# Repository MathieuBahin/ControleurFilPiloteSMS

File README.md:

# Controleur radiateur avec fil pilote par SMS

Bonjour à tous je vous propose aujourd'hui un projet pour contrôler un radiateur par SMS. Le radiateur doit posséder l'option "Fil pilote".

Mon besoin est de pouvoir piloter la mise en marche d'un radiateur situé dans une résidence secondaire à distance. L'idée est de pouvoir envoyer un ordre à une unité réceptrice qui va allumer le radiateur et me permettre d'arriver 1/2 jours plus tard avec une température correcte dans la résidence.

Des produits similaires existent mais la plupart proposent une communication par Internet, non compatible avec la configuration de la résidence secondaire.

Attention vous allez manipuler des courants mortels je vous conseille une grande vigilance lors des manipulations.

## Electronique

### La communication par fil pilote
On retrouve ci-dessous les commandes pour piloter le radiateur :

[Source](https://www.planete-domotique.com/blog/2012/01/05/piloter-un-radiateur-grace-a-son-fil-pilote/)

Le radiateur est donc piloté grâce à la sinusoïde 230V.

Pour créer les demi-alternances positives et négatives on utilise les optocoupleurs et les diodes.

En effet une diode dans le sens passant du 230V créer une demi-alternance positive et une diode dans le sens non passant crée une demi-alternance négative. Les optocoupleurs permettent de choisir si le chemin positif, négatif ou les deux sont utilisés.

### Composants utilisés
Pour le projet voici les composants utilisés : 

| Nom                  |  Coût |
| --------------------- |:-----:|
| Arduino Nano x1          |   2€  |
| [SIM800L](https://www.amazon.fr/Sim800l-Quadribande-Embarqu%C3%A9e-Antenne-Arduino/dp/B01FQPLG9W) x1     | 6€ |
| [DS18B20](https://www.amazon.fr/ANGEEK-capteurs-temp%C3%A9rature-num%C3%A9riques-TO92-55%C2%B0C/dp/B07VB25GS5/) x1        |  8€ pour 5 |
| [IRM-10-5](https://fr.rs-online.com/web/p/alimentations-a-decoupage/1358929/)    x1        |  10€   |
| [ZFKDS gauche](https://fr.rs-online.com/web/p/borniers-pour-circuits-imprimes/8045105/)  x1    | 0.50€ |
| [ZFKDS droit](https://fr.rs-online.com/web/p/borniers-pour-circuits-imprimes/8045102/)   x1  | 16.70€ pour 50 |
| [MOC3043M](https://fr.rs-online.com/web/p/optocoupleurs/1611159) x2    | 7.76€ pour 10 |
| Résistance 4.7k     | |
| Résistance 1.8k     | |
| Résistance 1k     | |
| Résistance 680     | |
| Diode 1N4007 x3    | |
| Condensateur 470µF [Farnell](https://fr.farnell.com/panasonic-electronic-components/eeufr0j471/condensateur-470-f-6-3v-20/dp/2805615)     | |

Le capteur de température et la résistance R9 associée sont optionnels.
Les connecteurs ZFKDS peuvent être remplacés par des borniers etc.
Le condensateur n'est pas optionnel.
Le microcontrôleur Arduino est remplaçable par d'autres (par exemple un PIC8F ou autres) mais le code ne sera pas portable sur les autres plateformes telles quelles.

## Projet KiCad
Les fichiers KiCad sont situés dans le dossier KiCad. Les PCB sont gravés chez [JLCPCB](https://jlcpcb.com/).

Attention pour le module SIM800L a la tension d'alimentation qui est spéciale. J'utilise la tension de chute de la diode pour l'alimenter selon la datasheet. Un pont diviseur est également nécessaire pour la communication UART (5V → 3.3V).

Une fois le PCB reçu je vous conseille de souder le transformateur en dernier.

Si vous souhaitez faire une vérification sur le 230V à la sortie du fil pilote noté que votre multimètre ne vous indiquera pas 115V et si vous souhaitez vérifier avec un oscilloscope faite attention à utiliser une sonde différentielle !

## Développement Arduino
Vous pouvez utiliser l'IDE de votre choix j'utilise personnellement l'IDE Arduino.

Ajoutez les librairies dans votre dossier Arduino (généralement Documents\Arduino\libraries) sinon depuis l'IDE "Croquis → Inclure une bibliothèque"

Dans Outil choisissez votre carte : Arduino Nano et le processeur qui correspond à votre carte.

Puis connectez votre Arduino et flashez le programme.

Vous pouvez ouvrir le moniteur série à 9600 pour voir l'initialisation des composants.

Attention à remplir le numéro de téléphone ou vous souhaitez recevoir les sms. La carte SIM ne doit pas avoir de code PIN.

## Boitier

J'ai choisi un boitier de dérivation de 110x110mm. Vous pouvez soit fixer la carte électronique au fond avec des vis / écrous ou mettre un point de colle dans les coins.

## Installation

N'inversez pas la phase et le neutre, pour différencier les fils (en faisant très attention) munissez-vous de votre multimètre et prenez pour référence la terre.

Phase + terre environ égale à 230V

Neutre + terre environ égale à 0V

Le PCB n'a pas de protection contre les inversions, il est indispensable de brancher la phase sur l'entrée phase sinon le fil pilote ne fonctionnera pas. 

Sectionnez le fil de phase et le fil de neutre (en ayant disjoncté), ajouter un domino de 3 sur la phase et 3 sur le neutre. Branchez le fil pilote du radiateur directement sur la carte. La phase venant du mur va dans le domino qui repart en 2 fils, vers le boitier et vers le radiateur. Idem pour le neutre.

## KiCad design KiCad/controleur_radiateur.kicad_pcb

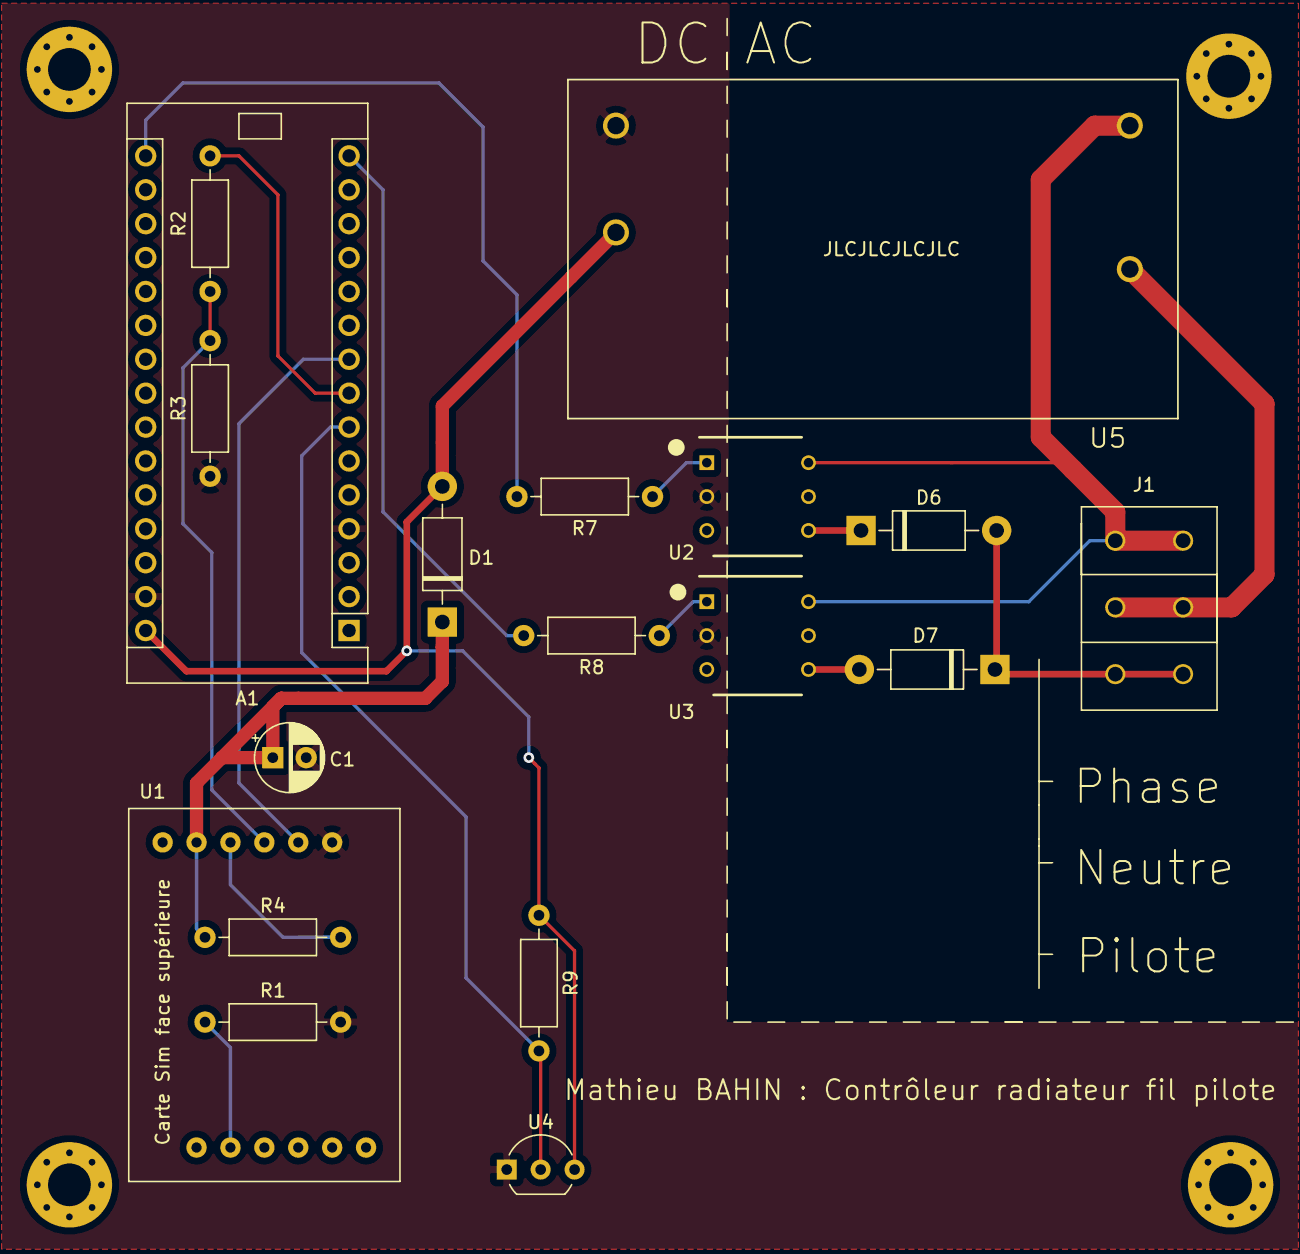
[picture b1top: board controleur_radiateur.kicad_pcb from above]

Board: 2 copper layers, 18 parts (0 on the bottom side), 18 nets.

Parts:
A1: Arduino_Nano_v3.x; Arduino_Nano_step
C1: 100u 10V; CP_Radial_D5.0mm_P2.50mm
D1, D6, D7: 1N4007; D_DO-41_SOD81_P10.16mm_Horizontal
J1: ZFKDS_3
R1, R4, R9: 4.7k; R_Axial_DIN0207_L6.3mm_D2.5mm_P10.16mm_Horizontal
R2: 1k; R_Axial_DIN0207_L6.3mm_D2.5mm_P10.16mm_Horizontal
R3: 1.8k; R_Axial_DIN0207_L6.3mm_D2.5mm_P10.16mm_Horizontal
R7, R8: 680; R_Axial_DIN0207_L6.3mm_D2.5mm_P10.16mm_Horizontal
U1: SIM800L; SIM800L_module
U2, U3: MOC3023M
U4: DS18B20; TO-92_Inline_Wide
U5: IRM-10-5

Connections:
+5V: A1.30, D1.2, R9.1, U4.3, U5.4
/D12: A1.15, R8.2
/D13: A1.16, R7.2
/RX_GSM: R2.1, R3.2, U1.4
/TX_GSM: A1.9, U1.5
/Temp_Data: A1.7, R9.2, U4.2
GND: A1.4, A1.29, C1.2, R1.2, R3.1, U1.6, U2.2, U3.2, U4.1, U5.3
unnamed: A1.8, R2.2
unnamed: C1.1, D1.1, R4.1, U1.2
unnamed: D6.1, U2.4
unnamed: D6.2, D7.1, J1.5, J1.6
unnamed: D7.2, U3.4
unnamed: J1.1, J1.2, U2.6, U3.6, U5.2
unnamed: J1.3, J1.4, U5.1
unnamed: R1.1, U1.8
unnamed: R4.2, U1.3
unnamed: R7.1, U2.1
unnamed: R8.1, U3.1

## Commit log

2021-06-23 Added pictures for the readme
2021-06-23 Ajout image commande pour l'explication sur le Readme
2021-06-23 Ajout des explications dans le Readme
2021-06-23 installation derrière le radiateur
2021-06-27 [ADD] fichier KiCad
2021-06-27 Pas de communication SMS pour le moment A FAIRE
2021-06-27 [+] libs
2021-06-27 [MAJ] modification pour les libs
2021-06-27 [+] librairie kicad
2021-06-27 [+] Doc ajouter librairie
2021-09-28 Communication, rechargement depuis EEPROM, mode pilote
    vérifier les define des set_Pilote
2021-09-28 Changement suite à l'ajout du code Arduino
2021-09-28 code PIN de la SIM désactiver
2021-11-02 [+] image montage Readme
2021-11-02 [+] instruction montage
2022-03-01 PCB : suppression des led, changement optocoupleurs pour des MOC3043M, redesign du PCB Soft : reconnection automatique toutes les 1 minutes au réseau GSM
